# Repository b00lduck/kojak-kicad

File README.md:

# kojak-kicad
Kojak-Sirene mit KiCad

## PCB-3D-Rendering

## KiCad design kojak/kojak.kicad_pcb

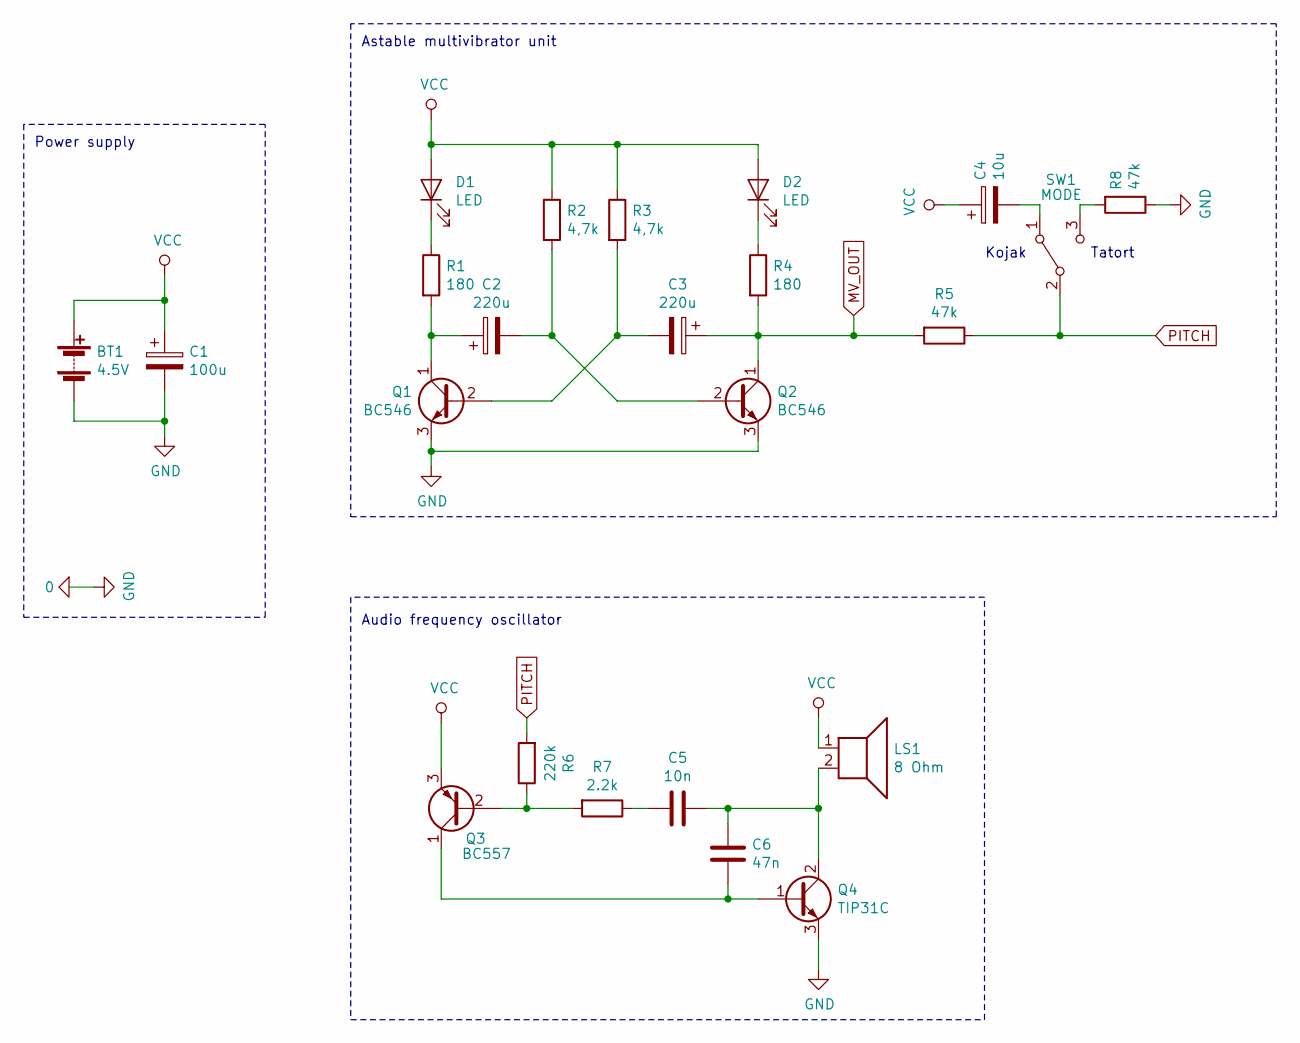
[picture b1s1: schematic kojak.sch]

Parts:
BT1: 4.5V; PinHeader_1x02_P2.54mm_Vertical
C1: 100u; CP_Radial_D10.0mm_P5.00mm
C2, C3: 220u; CP_Radial_D10.0mm_P5.00mm
C4: 10u; CP_Radial_D5.0mm_P2.50mm
C5: 10n; C_Disc_D5.0mm_W2.5mm_P5.00mm
C6: 47n; C_Disc_D5.0mm_W2.5mm_P5.00mm
D1, D2: LED; LED_D5.0mm
LS1: 8 Ohm; PinHeader_1x02_P2.54mm_Vertical
Q1, Q2: BC546; TO-92_Inline
Q3: BC557; TO-92_Inline
Q4: TIP31C; TO-220-3_Vertical
R1, R4: 180; R_Axial_DIN0207_L6.3mm_D2.5mm_P7.62mm_Horizontal
R2, R3: 4,7k; R_Axial_DIN0207_L6.3mm_D2.5mm_P7.62mm_Horizontal
R5, R8: 47k; R_Axial_DIN0207_L6.3mm_D2.5mm_P7.62mm_Horizontal
R6: 220k; R_Axial_DIN0207_L6.3mm_D2.5mm_P7.62mm_Horizontal
R7: 2.2k; R_Axial_DIN0207_L6.3mm_D2.5mm_P7.62mm_Horizontal
SW1: MODE; PinHeader_1x03_P2.54mm_Vertical

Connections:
GND: BT1.2 (-), C1.2, Q1.3 (E), Q2.3 (E), Q4.3 (E), R8.1
MV_OUT: C3.1, Q2.1 (C), R4.2, R5.2
unnamed: C2.1, Q1.1 (C), R1.2
unnamed: C2.2, Q2.2 (B), R2.2
unnamed: C3.2, Q1.2 (B), R3.2
unnamed: C4.2, SW1.1 (A)
unnamed: C5.1, C6.2, LS1.2, Q4.2 (C)
unnamed: C5.2, R7.1
unnamed: C6.1, Q3.1 (C), Q4.1 (B)
unnamed: D1.1 (K), R1.1
unnamed: D2.1 (K), R4.1
unnamed: Q3.2 (B), R6.1, R7.2
unnamed: R8.2, SW1.3 (C)
PITCH: R5.1, R6.2, SW1.2 (B)
VCC: BT1.1 (+), C1.1, C4.1, D1.2 (A), D2.2 (A), LS1.1, Q3.3 (E), R2.1, R3.1

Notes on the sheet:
Power supply
Astable multivibrator unit
Audio frequency oscillator
Kojak
Tatort

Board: 2 copper layers, 23 parts (0 on the bottom side), 15 nets, no tracks yet.

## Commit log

2019-12-04 Schaltplan und PCB-Files
2019-12-04 docs
2019-12-04 notes
2019-12-04 Image in readme
2019-12-04 image
2019-12-04 Readme image
2019-12-04 PCB-Rendering
2019-12-04 Readme
2019-12-04 Remove tracks
2019-12-04 remove board
2019-12-04 remove annoations and footprints
2019-12-04 prune project
2019-12-04 add case cad files
2019-12-05 rescue
